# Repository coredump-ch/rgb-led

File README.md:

# RGB LED

An RGB LED board, originally developed in fall 2014 by coredump hackerspace in
Rapperswil, Switzerland for teaching kids (~10y) the basics of electronics.

## Version 1

The v1 consists of a potentiometer for each RGB color. The current is only
controlled by the potentiometers. Therefore not too many LEDs can be driven at
the same time.

In contrast to v2 the v1 is also missing a switch to turn on/off the power.

![foto v1][v1-photo-back]

## Version 2

The v2 is more advanced and uses an Arduino Nano as controller. The arduino
controls the RGB LEDs' brightness through PWM. The LEDs are switched with three
MOSFETs. This enables the control of more LEDs at the same time.

Project description is here: http://www.hackster.io/2460/arduino-controlled-rgb-led-strip

![foto v2][v2-photo]
![foto v2 pcb][v2-photo-pcb]
![schema v2][v2-schema]

## Licensing

See `LICENSE.md` file.

[v1-photo-back]: https://raw.githubusercontent.com/coredump-ch/rgb-led/master/v1/photo_v1_back.jpg
[v2-schema]: https://raw.githubusercontent.com/coredump-ch/rgb-led/master/v2/export/v2/schema.png
[v2-photo]: https://raw.githubusercontent.com/coredump-ch/rgb-led/master/v2/photo_v2.jpg
[v2-photo-pcb]: https://raw.githubusercontent.com/coredump-ch/rgb-led/master/v2/photo_v2_pcb.jpg

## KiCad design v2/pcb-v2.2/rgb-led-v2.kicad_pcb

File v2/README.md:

# Pinout

## LEDs

- Red: D3 / 1
- Green: D6 / 10
- Blue: D5 / 9

## Pots

- 1: A0 / 14
- 2: A1 / 15
- 3: A2 / 16

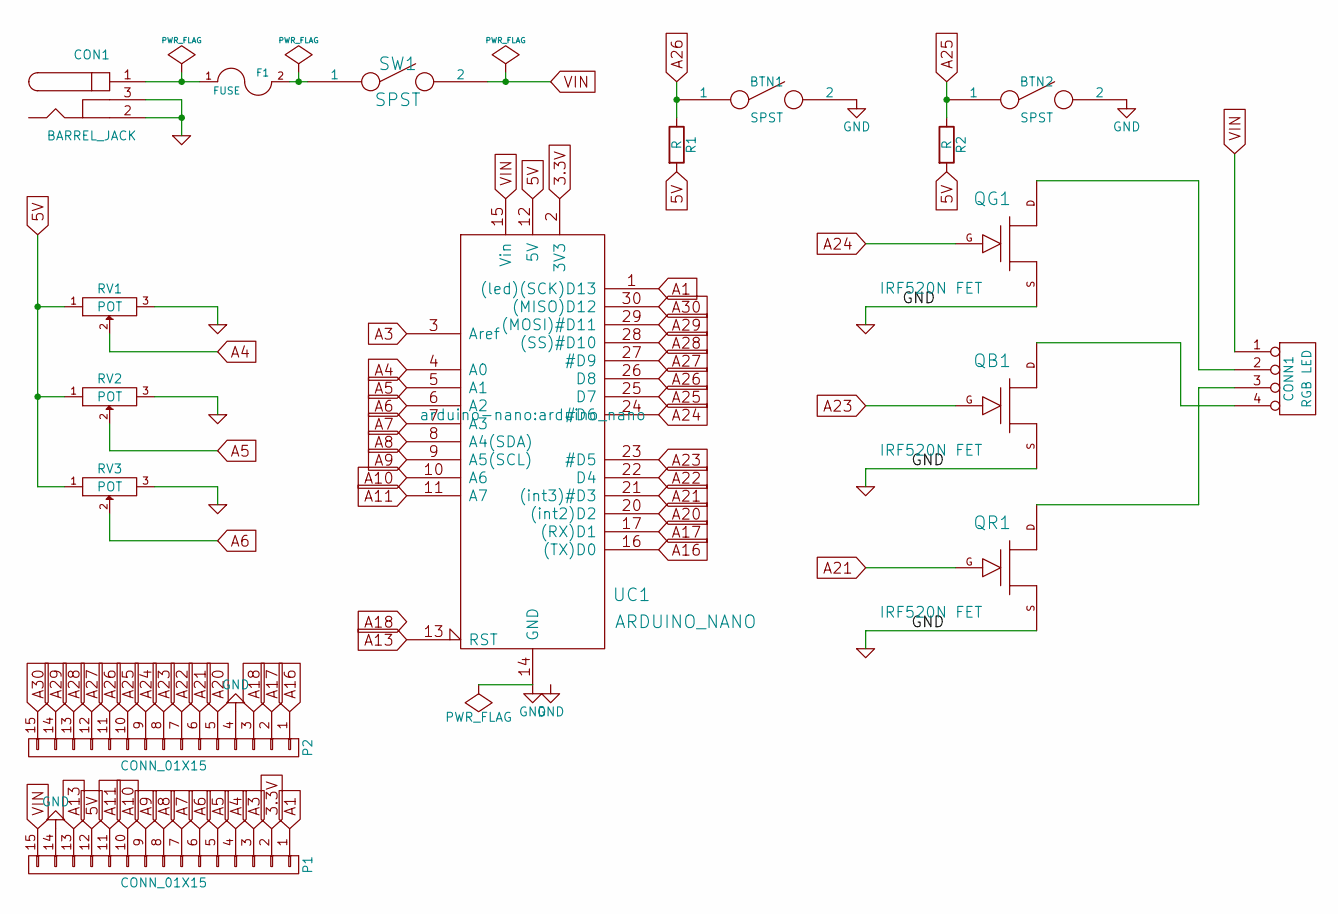
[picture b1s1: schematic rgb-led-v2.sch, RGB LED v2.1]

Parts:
BTN1, BTN2: SPST; PUSHBUTTON_TS044S
CON1: BARREL_JACK
CONN1: RGB LED; PIN_ARRAY_4x1_THICK
F1: FUSE; KCD3
P1, P2: CONN_01X15; Pin_Header_Straight_1x15_Pitch2.54mm
QB1: IRF520N FET; IRF520N
QG1: IRF520N FET; IRF520N
QR1: IRF520N FET; IRF520N
R1, R2: R; R_Axial_DIN0207_L6.3mm_D2.5mm_P10.16mm_Horizontal
RV1, RV2, RV3: POT; POT_3
SW1: SPST; Switch_SS-12F46
UC1: ARDUINO_NANO; arduino_nano

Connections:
3.3V: P1.2, UC1.2 (3V3)
5V: P1.12, R1.2, R2.2, RV1.1, RV2.1, RV3.1, UC1.12 (5V)
A1: P1.1, UC1.1 ((led)(SCK)D13)
A3: P1.3, UC1.3 (Aref)
A4: P1.4, RV1.2, UC1.4 (A0)
A5: P1.5, RV2.2, UC1.5 (A1)
A6: P1.6, RV3.2, UC1.6 (A2)
A7: P1.7, UC1.7 (A3)
A8: P1.8, UC1.8 (A4(SDA))
A9: P1.9, UC1.9 (A5(SCL))
A10: P1.10, UC1.10 (A6)
A11: P1.11, UC1.11 (A7)
A13: P1.13, UC1.13 (RST)
A16: P2.1, UC1.16 ((TX)D0)
A17: P2.2, UC1.17 ((RX)D1)
A18: P2.3, UC1.18 (RST)
A20: P2.5, UC1.20 ((int2)D2)
A21: P2.6, QR1.G, UC1.21 ((int3)#D3)
A22: P2.7, UC1.22 (D4)
A23: P2.8, QB1.G, UC1.23 (#D5)
A24: P2.9, QG1.G, UC1.24 (#D6)
A25: BTN2.1, P2.10, R2.1, UC1.25 (D7)
A26: BTN1.1, P2.11, R1.1, UC1.26 (D8)
A27: P2.12, UC1.27 (#D9)
A28: P2.13, UC1.28 ((SS)#D10)
A29: P2.14, UC1.29 ((MOSI)#D11)
A30: P2.15, UC1.30 ((MISO)D12)
GND: BTN1.2, BTN2.2, CON1.2, CON1.3, P1.14, P2.4, QB1.S, QG1.S, QR1.S, RV1.3, RV2.3, RV3.3, UC1.14 (GND), UC1.19 (GND)
unnamed: CON1.1, F1.1
unnamed: CONN1.2, QG1.D
unnamed: CONN1.3, QR1.D
unnamed: CONN1.4, QB1.D
unnamed: F1.2, SW1.1
VIN: CONN1.1, P1.15, SW1.2, UC1.15 (Vin)

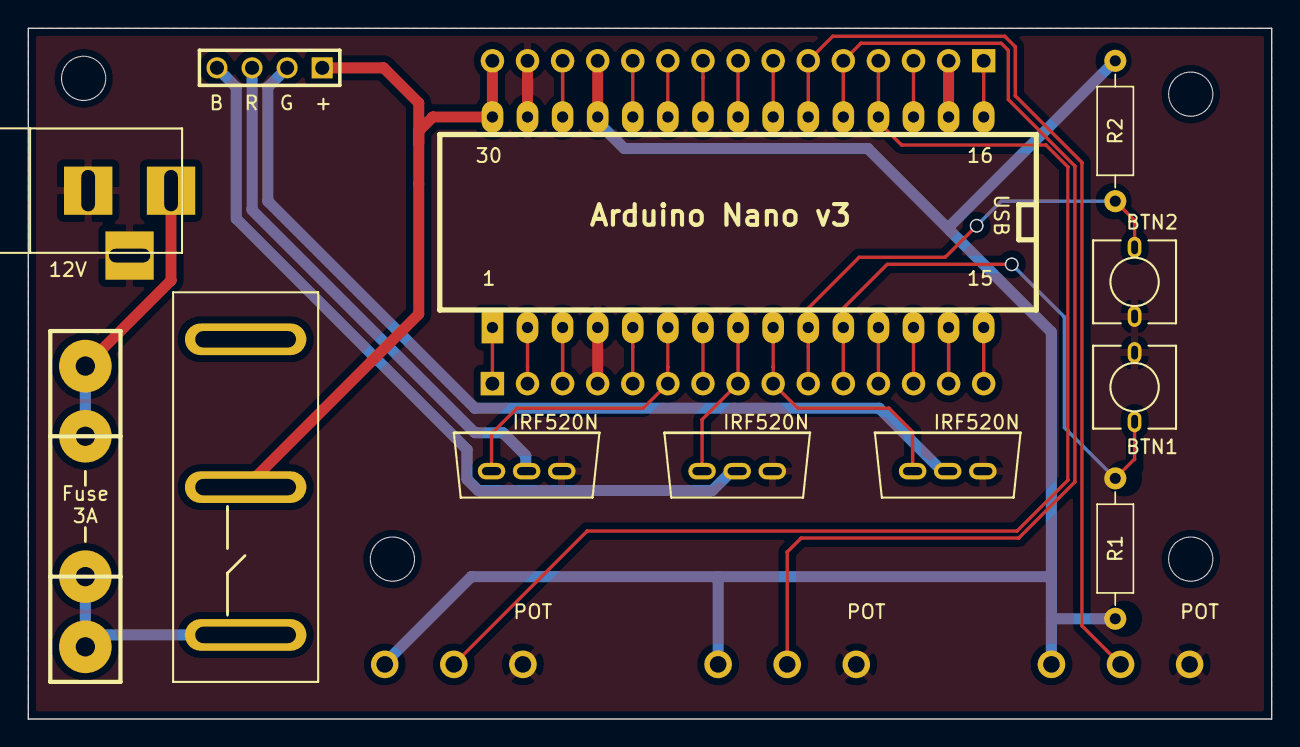
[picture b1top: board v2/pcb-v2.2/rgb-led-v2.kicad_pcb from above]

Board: 2 copper layers, 90.0 x 50.0 mm, 17 parts (0 on the bottom side), 34 nets.

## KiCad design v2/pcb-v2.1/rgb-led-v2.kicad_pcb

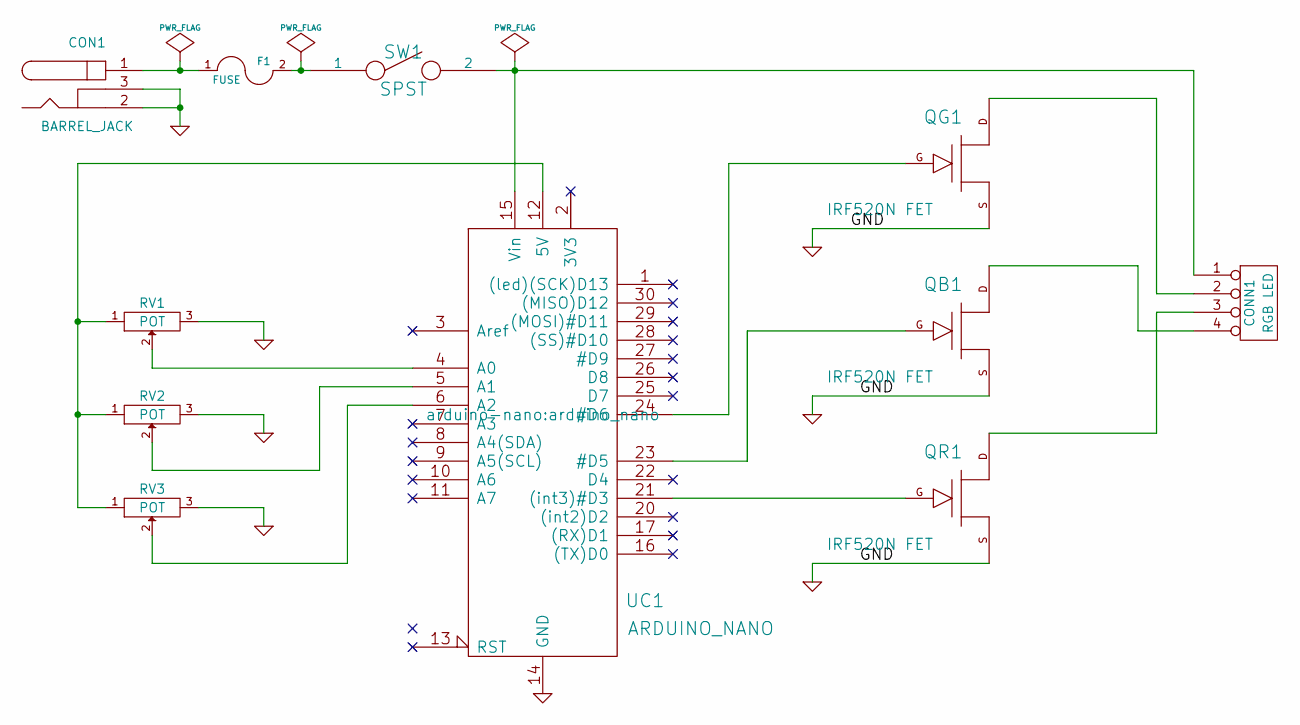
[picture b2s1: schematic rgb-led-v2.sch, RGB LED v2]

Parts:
CON1: BARREL_JACK
CONN1: RGB LED; PIN_ARRAY_4x1_THICK
F1: FUSE; KCD3
QB1: IRF520N FET; IRF520N
QG1: IRF520N FET; IRF520N
QR1: IRF520N FET; IRF520N
RV1, RV2, RV3: POT; POT_3
SW1: SPST; Switch_SS-12F46
UC1: ARDUINO_NANO; arduino_nano

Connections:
GND: CON1.2, CON1.3, QB1.S, QG1.S, QR1.S, RV1.3, RV2.3, RV3.3, UC1.14 (GND), UC1.19 (GND)
unnamed: CON1.1, F1.1
unnamed: CONN1.1, SW1.2, UC1.15 (Vin)
unnamed: CONN1.2, QG1.D
unnamed: CONN1.3, QR1.D
unnamed: CONN1.4, QB1.D
unnamed: F1.2, SW1.1
unnamed: QB1.G, UC1.23 (#D5)
unnamed: QG1.G, UC1.24 (#D6)
unnamed: QR1.G, UC1.21 ((int3)#D3)
unnamed: RV1.1, RV2.1, RV3.1, UC1.12 (5V)
unnamed: RV1.2, UC1.4 (A0)
unnamed: RV2.2, UC1.5 (A1)
unnamed: RV3.2, UC1.6 (A2)

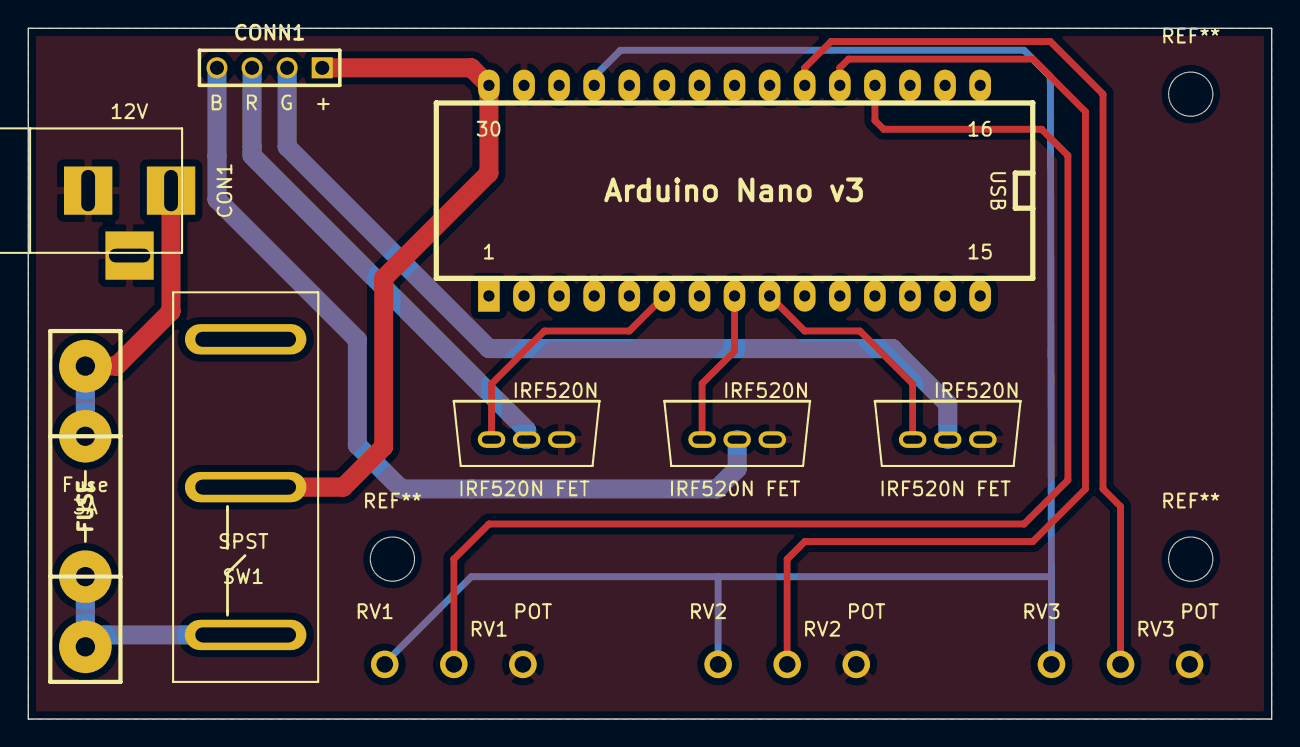
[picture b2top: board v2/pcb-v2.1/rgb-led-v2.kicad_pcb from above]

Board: 2 copper layers, 90.0 x 50.0 mm, 11 parts (0 on the bottom side), 14 nets.

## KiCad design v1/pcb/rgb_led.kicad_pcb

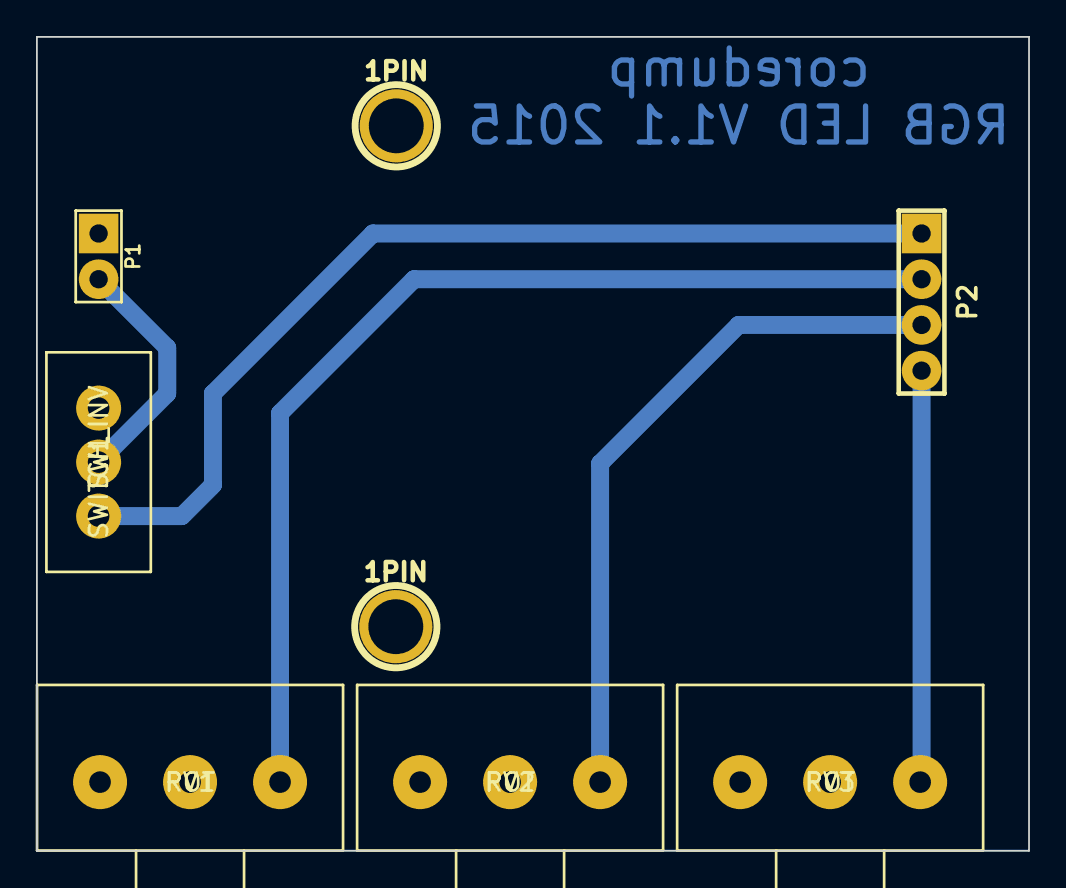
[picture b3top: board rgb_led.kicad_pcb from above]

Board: 2 copper layers, 55.1 x 45.2 mm, 8 parts (0 on the bottom side), 6 nets.

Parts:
1PIN, 1PIN#2: P***; 1pin
P1: CONN_2; PIN_ARRAY_2X1_THICK
P2: CONN_4; PIN_ARRAY_4x1_THICK
RV1, RV2, RV3: POT; POT_3_THICK
SW1: SWITCH_INV; Switch_SS-12F46

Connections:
GND: P1.1, RV1.1, RV1.2, RV2.1, RV2.2, RV3.1, RV3.2
unnamed: P2.4, RV3.3
unnamed: P2.3, RV2.3
unnamed: P2.2, RV1.3
unnamed: P2.1, SW1.1
VDD: P1.2, SW1.2

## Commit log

2014-10-21 Added pcb design
2014-10-21 Added potentiometer knobs
2014-10-21 Smaller page config for schema
2014-10-21 Added rendered version of schema
2014-10-21 Added potknob sources
2014-10-30 Added v2.0
2014-10-30 Version 2.1
2014-10-30 added photo of v1
2014-10-30 Update README.md
    added photo and v1 text
2014-10-30 Version 2.2
2014-11-01 Small tweaks on v2 project
2014-11-27 Moved around folders
2014-11-27 Started kicad version of v2
2014-11-27 Continued work on v2
2014-11-29 [library] Added IRF520 FET and KCD3 Switch
2014-11-29 [v2] Finished netlist assignment
2014-11-29 [v2] Started work on PCB layout
2014-11-30 [v2] Fixed references in PCB layout
2014-11-30 [v2] Configured track widths
2014-11-30 [v2] Added fuse
2014-11-30 [v2] Added 3d version of irf520n
2014-11-30 [v2] PCB Routing
2014-11-30 [V2] Updated README
2014-12-01 [v2] Improved PCB
2014-12-01 [v2] Removed outline of pot
2014-12-01 [v2] Added Gerber version
2014-12-01 [v2] Removed old Fritzing project
2014-12-01 [v2] Fixed library path
2014-12-01 [library] Added meshconv binary
2014-12-01 [v2] Exported PNG files
2014-12-01 Translated and extended README
2014-12-01 Clarified license
2014-12-01 Fixed links in LICENSE.md
2014-12-04 [v2] AVR C code for firmware
2014-12-05 [v2] Implemented first fading demo
2014-12-05 Added firmware license
2014-12-05 [v2] Added USART library
2014-12-05 [v2] Added HSI-RGB conversion functions
2014-12-23 Simplified colors.c
2014-12-23 HSI loop with pot input
2015-02-11 Added more v2 details
2015-02-11 Fixed wrong image URLs
2015-02-11 [v2] Moved PCB files to subdirectory
2015-02-11 [v2] Fixed kicad library path
2015-02-11 [v2] Widened holes in KCD3 footprint
2015-02-11 [v2] Created version 2.1
2015-08-14 [v2] Fixed Arduino makefile
2015-08-14 Updated .gitignore
2015-08-14 [v2] Switched to .ino files
2015-08-14 [v2] Split up firmware code into multiple files
2015-08-14 [v2] colors: Add C++ support
    For C++ we need to declare the functions as extern "C". Also remove the
    unneeded extern declaration, which is the default for functions.
2015-08-14 [v2] Add rgb_control effect
2015-08-14 [v2] rgb_control: Fix reading of the third poti
2015-08-14 [v2] Changed colors.{c,h} to hsi.{c,h}
2015-08-14 [v2] Basic implementation of color wheel
2015-08-14 [v2] Add blue sinus effect
2015-08-14 [v2]: blue_sin: Fix calculation of val_b
2015-08-14 [v2] Finished HSI version of colorwheel
2015-08-15 [v2] blue_sin: Use an exponential scale
2015-08-15 [v2] rgb_control: Scale poti inputs correctly
    The potis are mounted in a way that makes them intuitively inverted. So
    we adjust it in the code.
2015-08-15 [v2] Make it arduino IDE compatible
    Arduino needs to have the main entry file named the same like to folder
    it resides. Also it needs everything in a flat structure.
2015-08-15 [v2] make: Remove now unneeded effects folder
2015-08-15 added hsi_control
2015-08-19 add comments about range mapping and some brackets
2015-08-26 Moved firmware to separate repo
2015-09-22 Fixed library path in v1 pcb
2015-09-22 v1: Add Switch to schematic
2015-09-22 v1: Add switch to PCB and make it a bit smaller
2015-09-22 library: Add footprint for SS-12F46 switch
    See http://mikroshop.ch/Zubehoer.html?gruppe=10&artikel=483
2015-09-23 [v1] Adjusted date and version on PCB
2015-09-23 Increased distance between battery holes
    9V battery length is 26.5mm.
2015-09-24 Made board smaller
2015-09-24 Changed color labels to letters only
2015-09-24 Added OSHW logo
2015-09-24 Fixed edge cut
2015-09-24 Changed footprint page size to A4
2015-09-24 Actually fixed edge cuts
2015-09-24 Straightened fill zone
2015-09-24 Increased font size for pot labels
2015-09-24 Updated ground plane
    - Moved all text and image content to the copper layer
    - Added a zone cutout for the top part
2015-09-24 Made footprints thicker
2015-09-24 Made border a bit nicer
2015-10-05 Added newer version of pot knobs
2016-08-13 Update pcb-v2.1 to kicad4
    I just opened the project with kicad4 and it needed to change some
    components and I needed to remove the "special" library. Also kicad
    created a "rescue" library.
2016-08-24 Open project again and save it
    At this point I'm a bit confused about what KiCad is doing exactly...
2016-08-29 Add KiCad cache library
    The cache library contains all parts used in the schematic and PCB. If
    we want to make sure we are able to open the project across library
    versions on different machines we need to add it.
2016-08-30 Fixed power flags to make ERC happy
2016-09-04 PCB: Remove unnecessary vias
2016-09-04 Make pads for switch bigger
    Fixes #7
2016-09-15 Add DC jack
    Fixes #1
2016-09-19 Update metadata and text label
2016-09-19 Move open hardware logo and improve spacing
2016-09-19 Add mounting holes
2016-10-14 Replace tabs with 2 spaces
2016-10-14 Knob v3
2016-10-19 Add photo of kit
2016-10-19 Add numbers to kit photo
2016-10-19 Two more photos
2017-02-19 Add v2.2
2017-02-19 Add another mounting hole
2017-02-19 3D paths
2017-02-19 Improved routing, thinner traces
2017-02-19 Add pin headers to schema
2017-02-19 Add pin headers to Arduino
2017-02-19 Add pin headers to PCB
2017-02-19 Made switch holes a bit wider again
2017-02-19 Two push buttons (fixes #2)
2017-02-19 More spacing between pin headers and Arduino
2017-02-20 Add gerber output for v2.1
2017-02-20 Align resistors
2017-02-20 More resistor alignment
